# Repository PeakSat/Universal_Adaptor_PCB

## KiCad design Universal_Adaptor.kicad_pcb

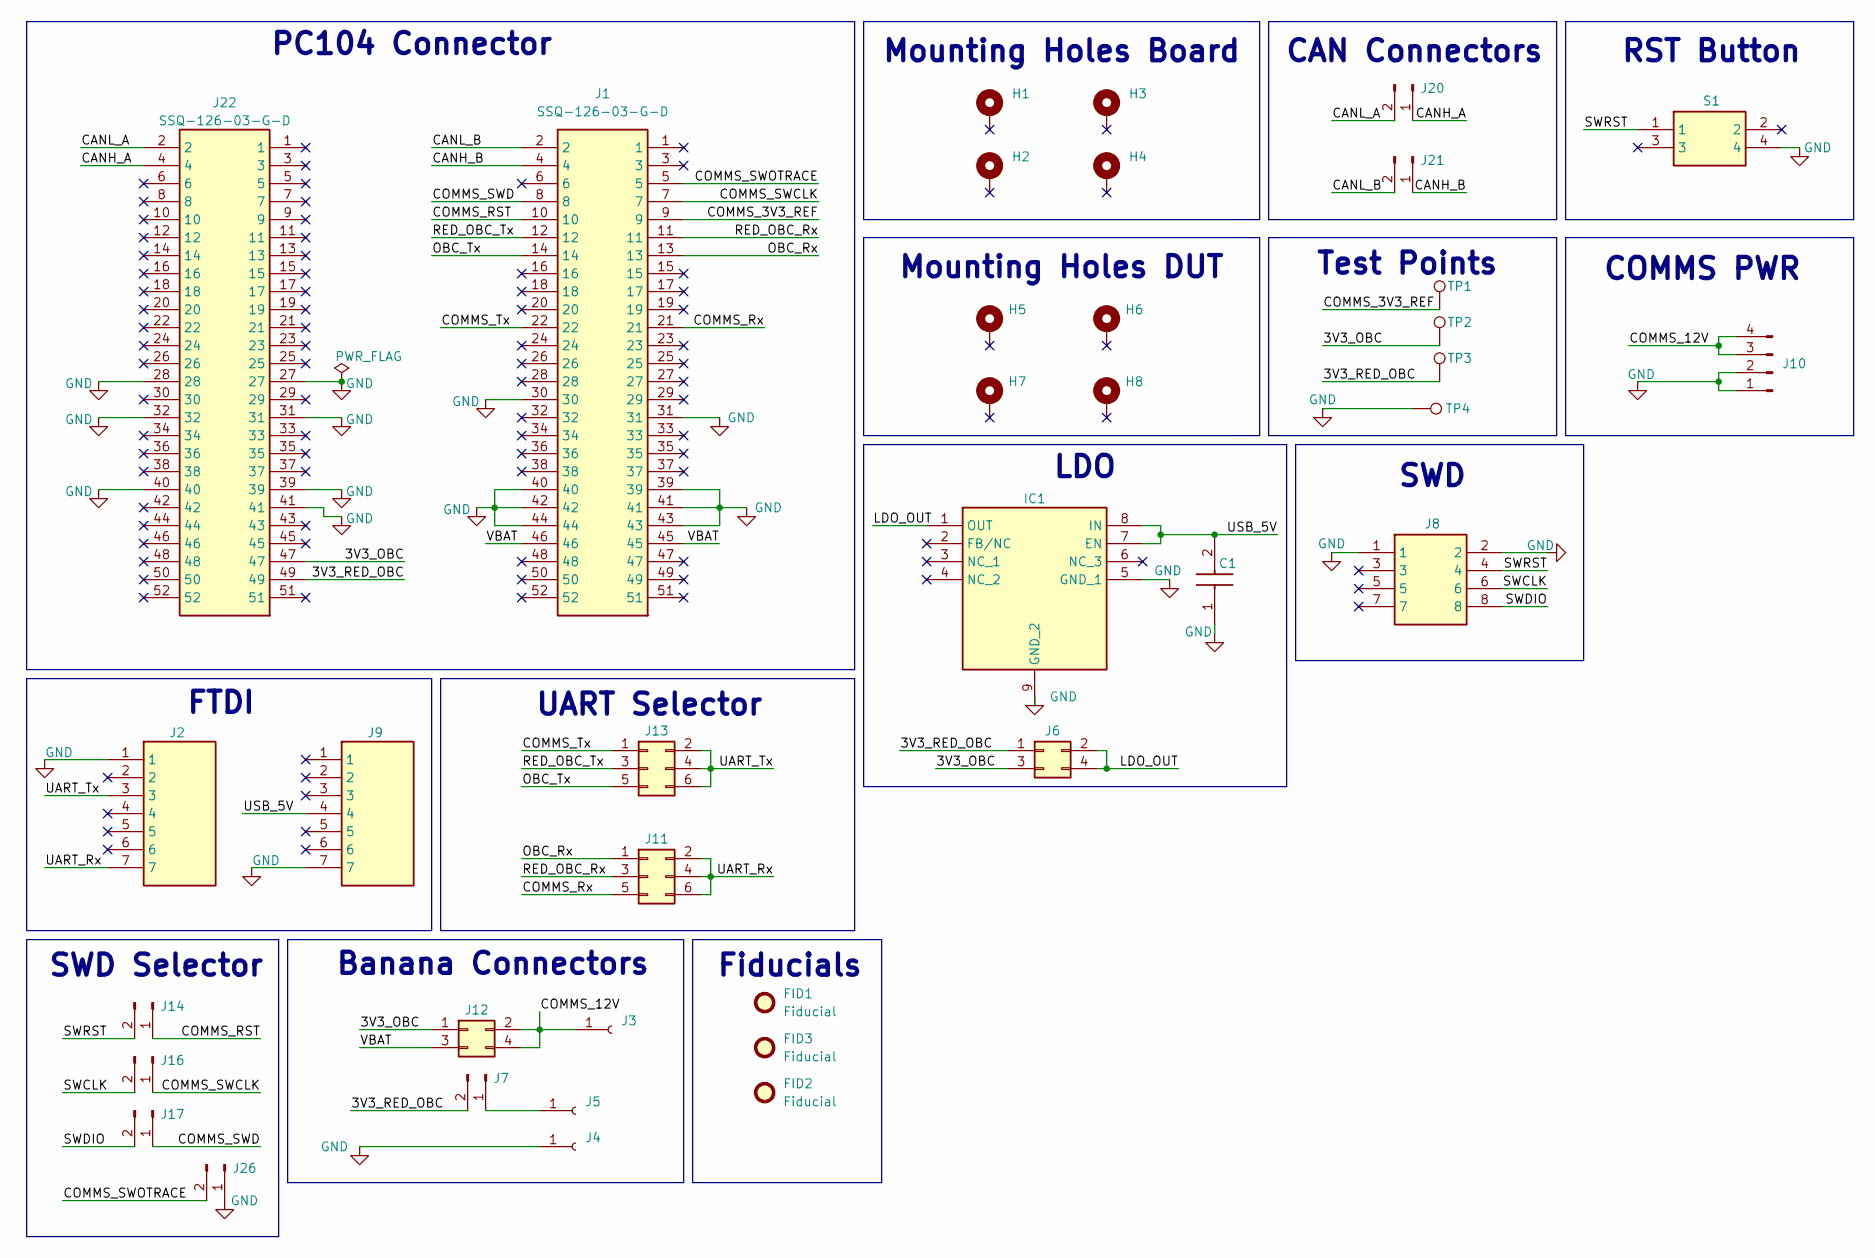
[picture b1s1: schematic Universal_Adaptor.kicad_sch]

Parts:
C1: KAF21KR71H105KU; CAPC2012X140N; Mouser Part Number 581-KAF21KR71H105KU
FID1, FID2, FID3: Fiducial; Fiducial_0.5mm_Mask1mm
H1, H2, H3, H4, H5, H6, H7, H8: MountingHole_Pad; MountingHole_3.2mm_M3_DIN965_Pad
IC1: TPS7B8633QDDARQ1; SOIC127P600X170-9N; Mouser Part Number 595-TPS7B8633QDDARQ1
J1, J22: SSQ-126-03-G-D; SSQ-126-XX-YYY-D; Mouser Part Number 200-SSQ12603GD
J2, J9: TSW-107-24-L-S; TSW-107-XX-YY-S; Manufacturer_Part_Number TSW-107-24-L-S
J3, J4, J5: Conn_01x01_Socket; Banana_Jack_1Pin
J6, J12: Conn_02x02_Odd_Even; PinHeader_2x02_P2.54mm_Vertical
J7, J14, J16, J17: Conn_01x02_Pin; PinHeader_1x02_P2.54mm_Vertical
J8: DF11-8DP-2DSA_24_; SHDR8W60P200_2X4_1000X500X690P; Mouser Part Number 798-DF11-8DP-2DSA24
J10: Conn_01x04_Pin; PinHeader_1x04_P2.54mm_Vertical
J11, J13: Conn_02x03_Odd_Even; PinHeader_2x03_P2.54mm_Vertical
J20, J21, J26: Conn_01x02_Pin; PinSocket_1x02_P2.54mm_Vertical
S1: FSM4JH; Mouser Part Number 506-FSM4JH
TP1, TP2, TP3, TP4: TestPoint; TestPoint_Pad_D2.0mm

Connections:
/3V3_OBC: J6.3, J12.1, J22.47, TP2.1
/3V3_RED_OBC: J6.1, J7.2, J22.49, TP3.1
/CANH_A: J20.1, J22.4
/CANH_B: J1.4, J21.1
/CANL_A: J20.2, J22.2
/CANL_B: J1.2, J21.2
/COMMS_3V3_REF: J1.9, TP1.1
/COMMS_12V: J3.1, J10.3, J10.4, J12.2, J12.4
/COMMS_RST: J1.10, J14.1
/COMMS_Rx: J1.21, J11.5
/COMMS_SWCLK: J1.7, J16.1
/COMMS_SWD: J1.8, J17.1
/COMMS_SWOTRACE: J1.5, J26.2
/COMMS_Tx: J1.22, J13.1
/LDO_OUT: IC1.1 (OUT), J6.2, J6.4
/OBC_Rx: J1.13, J11.1
/OBC_Tx: J1.14, J13.5
/RED_OBC_Rx: J1.11, J11.3
/RED_OBC_Tx: J1.12, J13.3
/SWCLK: J8.6, J16.2
/SWDIO: J8.8, J17.2
/SWRST: J8.4, J14.2, S1.1
/UART_Rx: J2.7, J11.2, J11.4, J11.6
/UART_Tx: J2.3, J13.2, J13.4, J13.6
/USB_5V: C1.2, IC1.7 (EN), IC1.8 (IN), J9.4
/VBAT: J1.45, J1.46, J12.3
GND: C1.1, IC1.5 (GND_1), IC1.9 (GND_2), J1.30, J1.31, J1.39, J1.40, J1.41, J1.42, J1.43, J1.44, J2.1, J4.1, J8.1, J8.2, J9.7, J10.1, J10.2, J22.27, J22.28, J22.31, J22.32, J22.39, J22.40, J22.41, J26.1, S1.4, TP4.1
unnamed: J5.1, J7.1

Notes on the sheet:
Mounting Holes Board
CAN Connectors
RST Button
SWD
LDO
Fiducials
UART Selector
SWD Selector
Mounting Holes DUT
Test Points
FTDI
PC104 Connector
Banana Connectors
COMMS PWR

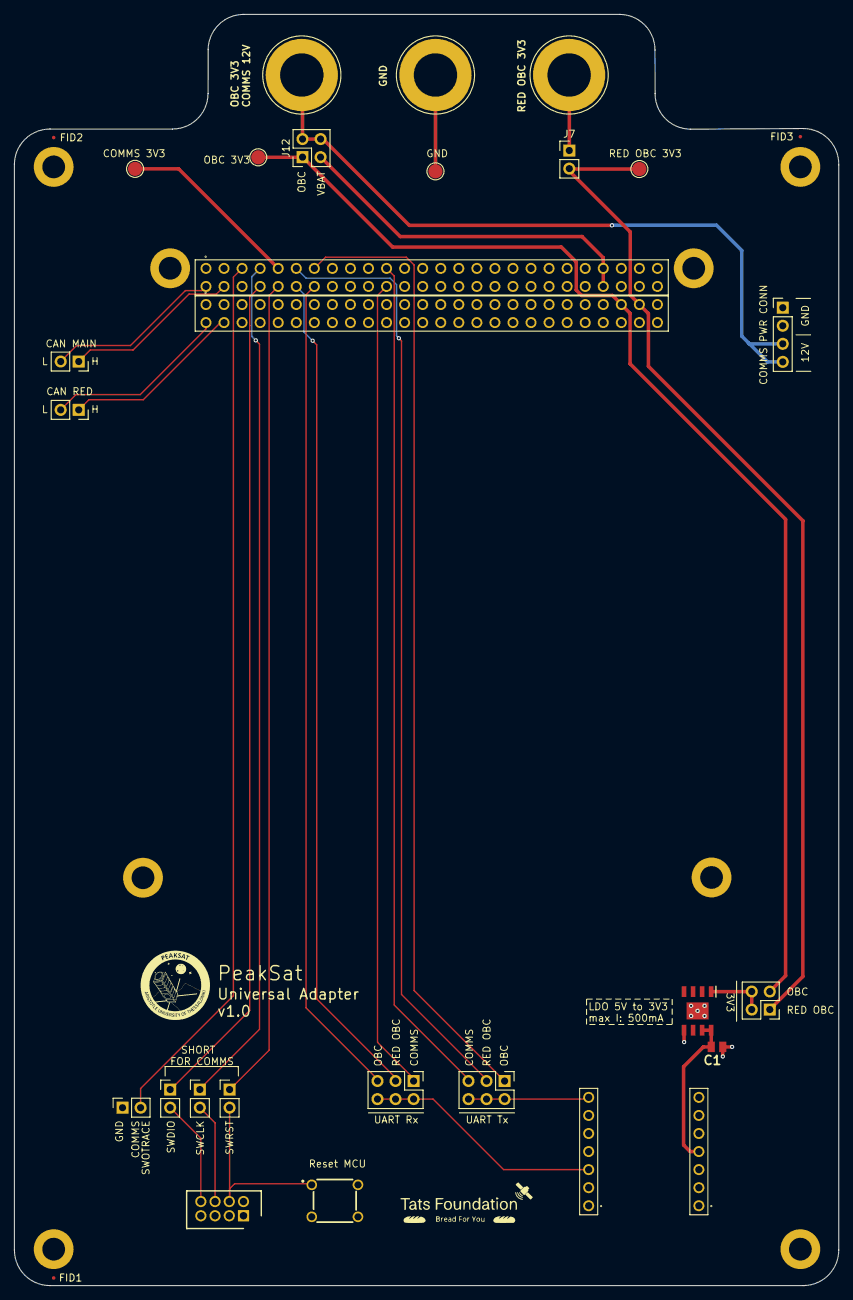
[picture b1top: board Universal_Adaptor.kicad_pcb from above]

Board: 2 copper layers, 116.0 x 178.8 mm, 38 parts (0 on the bottom side), 28 nets.

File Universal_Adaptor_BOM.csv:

Id;Designator;Footprint;Quantity;Designation;Supplier and ref
1;J13,J11;PinHeader_2x03_P2.54mm_Vertical;2;Conn_02x03_Odd_Even;-
2;J6,J12;PinHeader_2x02_P2.54mm_Vertical;2;Conn_02x02_Odd_Even;-
3;J14,J17,J16,J7;PinHeader_1x02_P2.54mm_Vertical;4;Conn_01x02_Pin;-
4;J26,J20,J21;PinSocket_1x02_P2.54mm_Vertical;3;Conn_01x02_Pin;-
5;TP2,TP3,TP1,TP4;TestPoint_Pad_D2.0mm;4;TestPoint;-
6;H7,H6,H8,H3,H5,H4,H1,H2;MountingHole_3.2mm_M3_DIN965_Pad;8;MountingHole_Pad;-
7;J9,J2;TSW-107-XX-YY-S;2;TSW-107-24-L-S;https://gr.mouser.com/ProductDetail/Samtec/TSW-107-24-L-S?qs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
8;J8;SHDR8W60P200_2X4_1000X500X690P;1;DF11-8DP-2DSA_24_;https://www.mouser.co.uk/ProductDetail/Hirose-Connector/DF11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
9;C1;CAPC2012X140N;1;KAF21KR71H105KU;https://www.mouser.co.uk/ProductDetail/KYOCERA-AVX/KAF21KR71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
10;J4,J5,J3;Banana_Jack_1Pin;3;Conn_01x01_Socket;-
11;J10;PinHeader_1x04_P2.54mm_Vertical;1;Conn_01x04_Pin;-
12;IC1;SOIC127P600X170-9N;1;TPS7B8633QDDARQ1;https://gr.mouser.com/ProductDetail/Texas-Instruments/TPS7B8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
13;J1,J22;SSQ-126-XX-YYY-D;2;SSQ-126-03-G-D;https://www.mouser.co.uk/ProductDetail/Samtec/SSQ-126-03-G-D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
14;S1;FSM4JH;1;FSM4JH;https://www.mouser.co.uk/ProductDetail/TE-Connectivity-Alcos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

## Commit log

2024-11-07 Added LDO to power OBC/RedOBC, Added jumper to connect 12V to VBAT for AcubeSat's COMMS
2024-11-11 Added BOM, Added Manufacture files
